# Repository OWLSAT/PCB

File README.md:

# PCB
Place all PCB projects here. Make sure that each PCB project is completely constrained inside of a folder for each!

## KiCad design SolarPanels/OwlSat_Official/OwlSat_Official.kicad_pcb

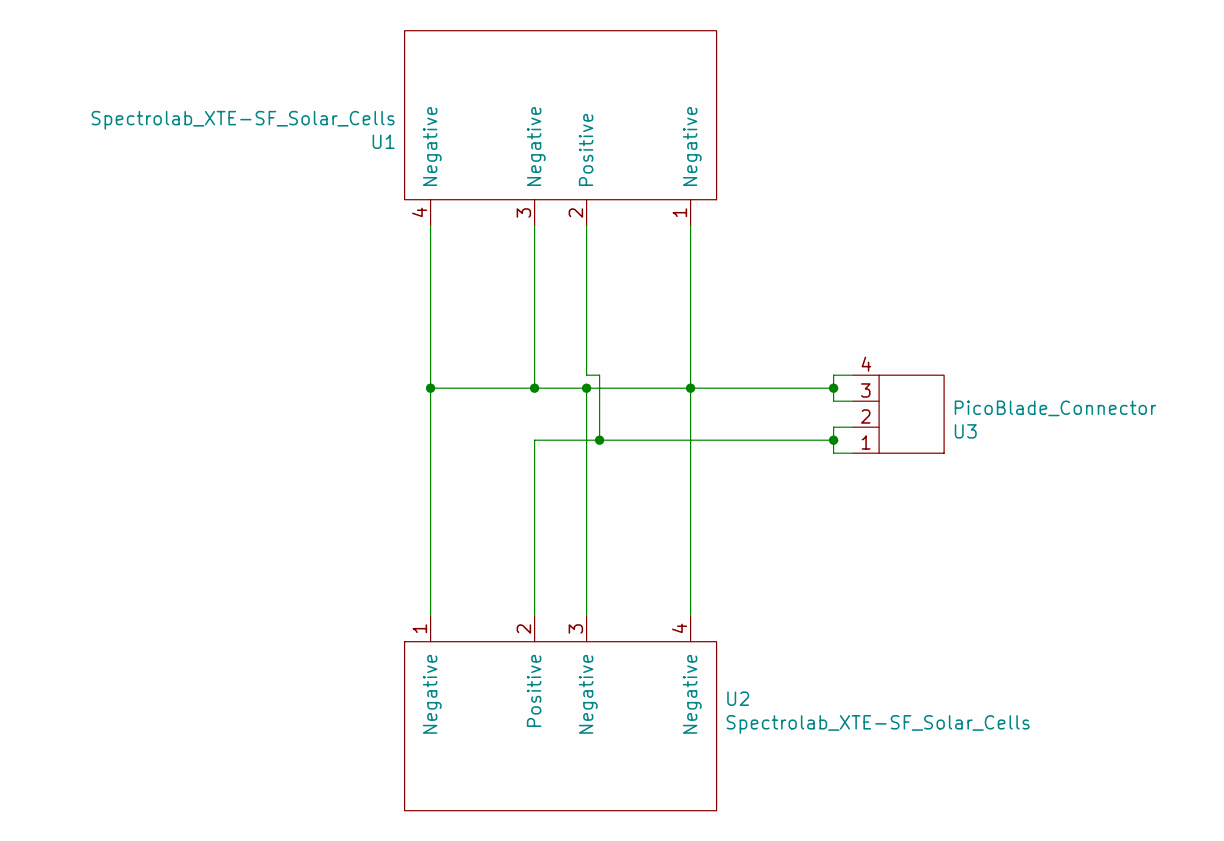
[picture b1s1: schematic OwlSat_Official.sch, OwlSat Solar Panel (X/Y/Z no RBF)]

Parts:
U1, U2: Spectrolab_XTE-SF_Solar_Cells; Spectrolab_XTE-SF_Solar_Cell
U3: PicoBlade_Connector; Molex_PicoBlade_53261-0471_1x04-1MP_P1.25mm_Horizontal

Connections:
unnamed: U1.1 (Negative), U1.3 (Negative), U1.4 (Negative), U2.1 (Negative), U2.3 (Negative), U2.4 (Negative), U3.3, U3.4
unnamed: U1.2 (Positive), U2.2 (Positive), U3.1, U3.2

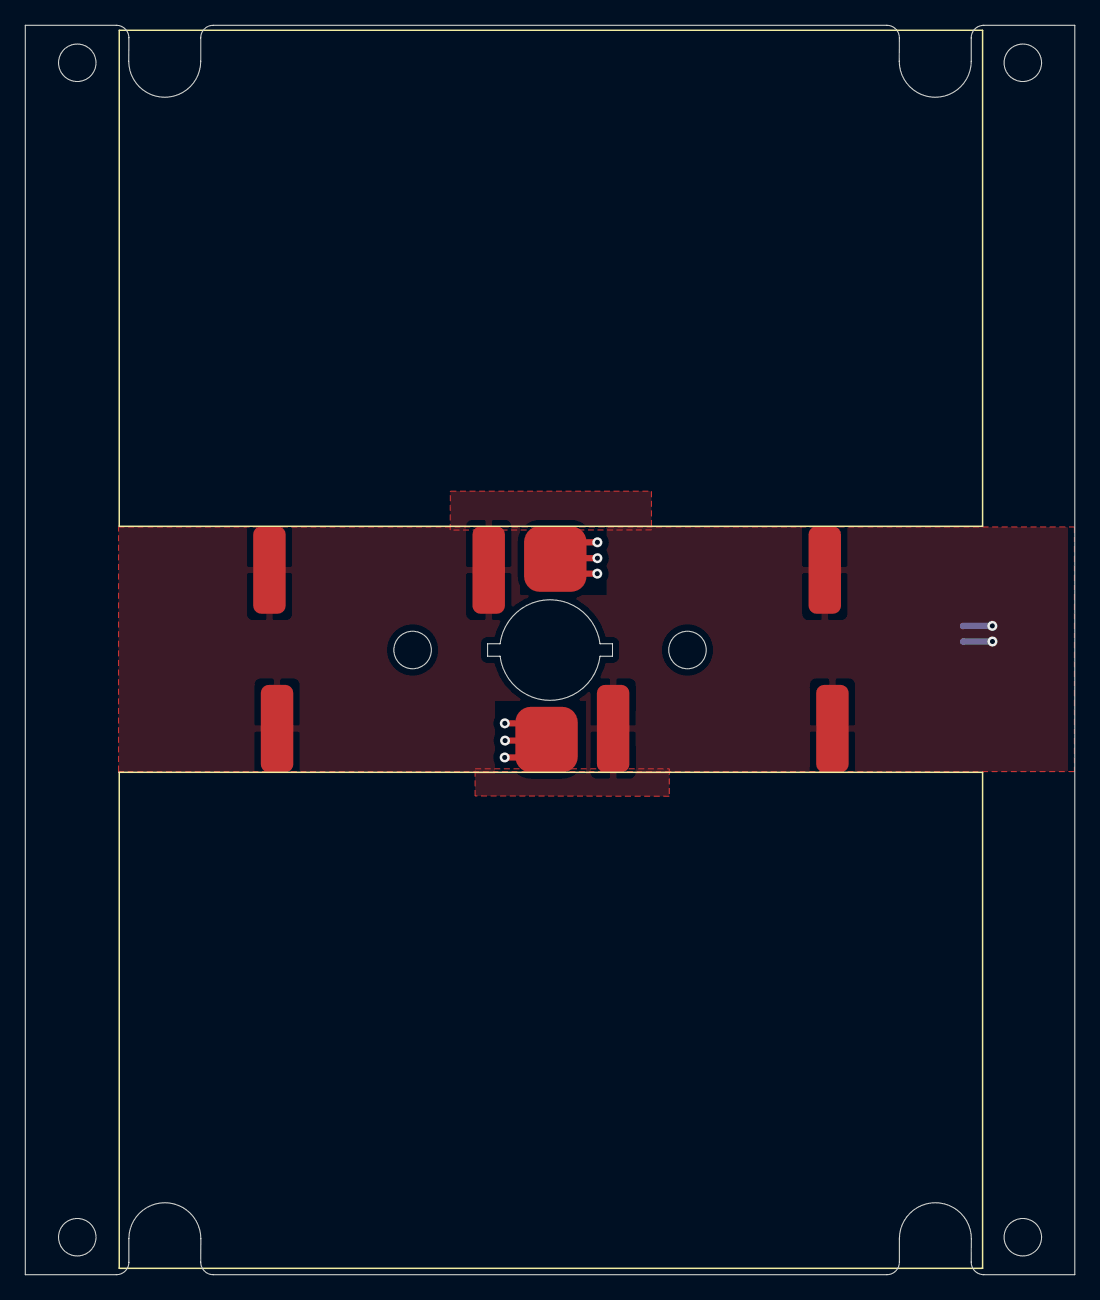
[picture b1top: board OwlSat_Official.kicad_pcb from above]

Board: 2 copper layers, 84.0 x 100.0 mm, 3 parts (1 on the bottom side), 2 nets.

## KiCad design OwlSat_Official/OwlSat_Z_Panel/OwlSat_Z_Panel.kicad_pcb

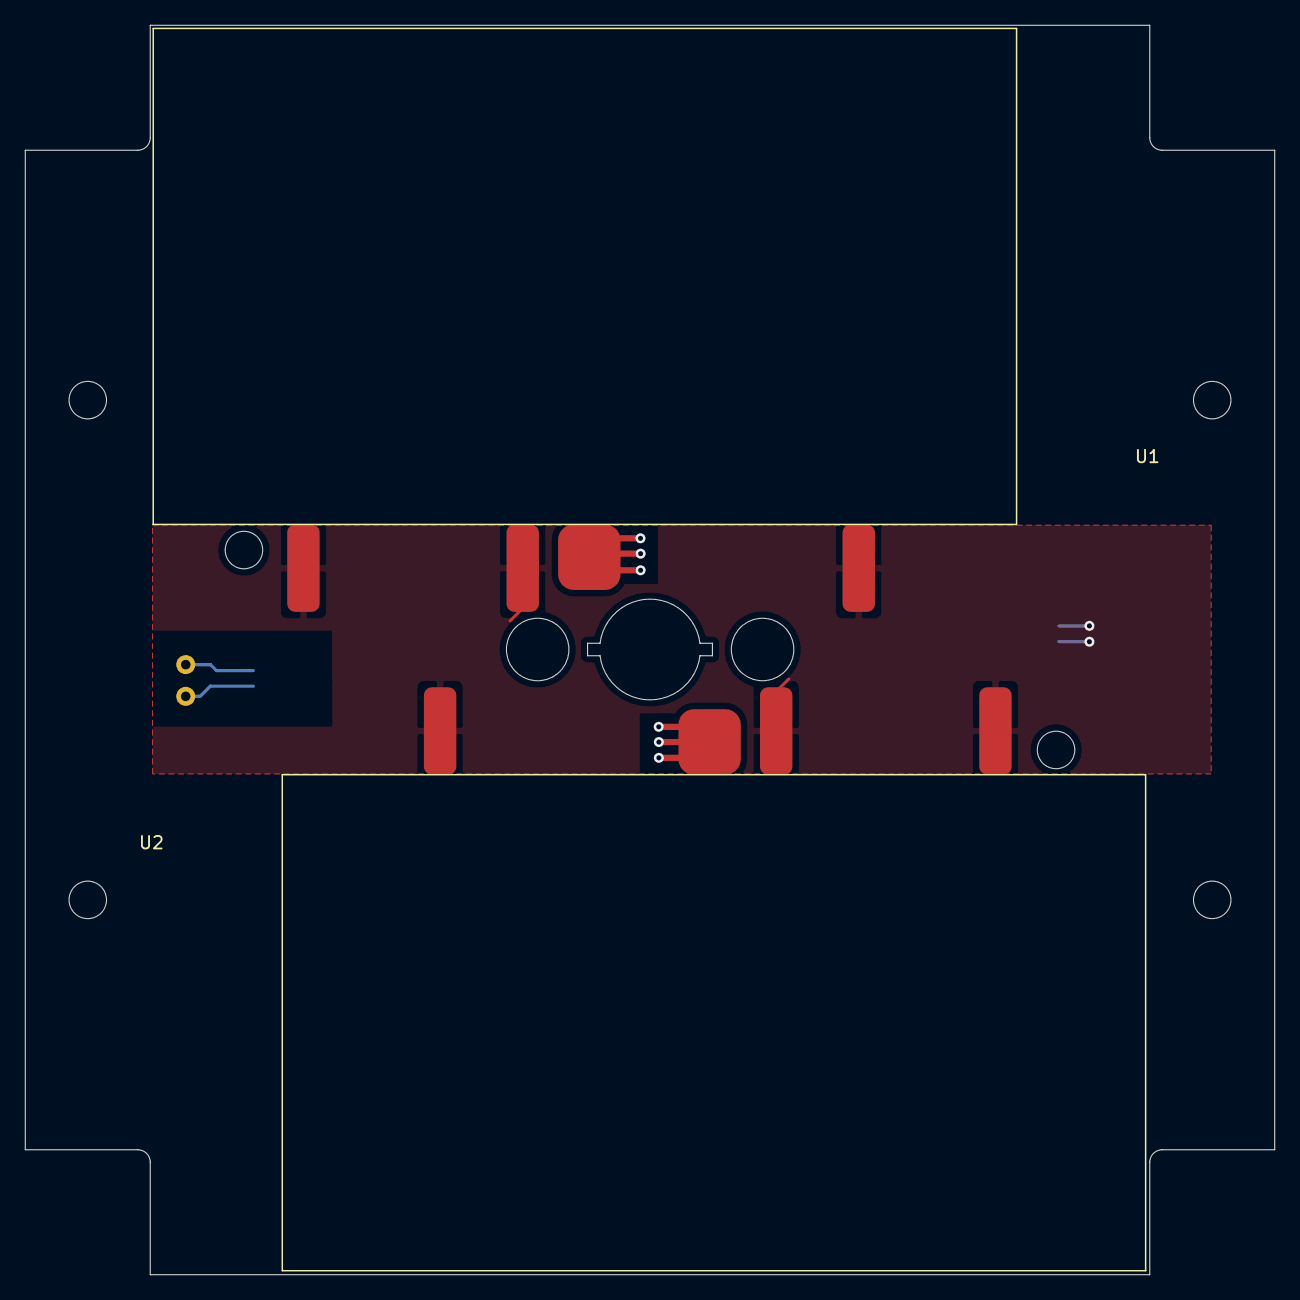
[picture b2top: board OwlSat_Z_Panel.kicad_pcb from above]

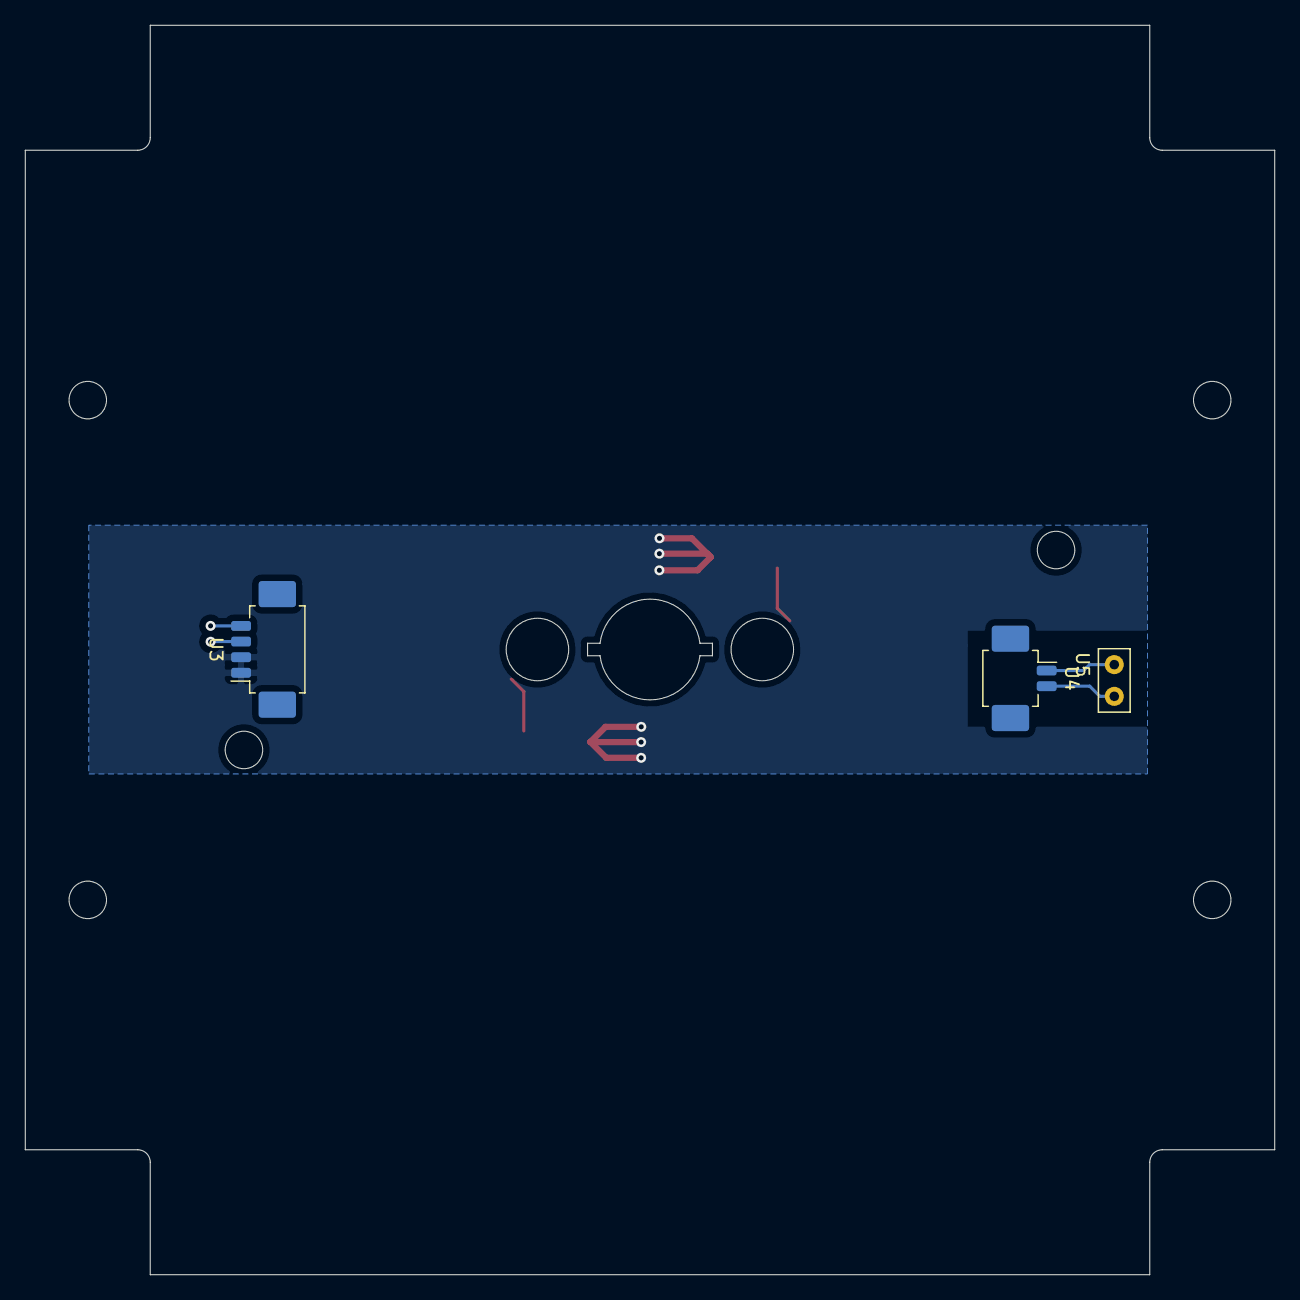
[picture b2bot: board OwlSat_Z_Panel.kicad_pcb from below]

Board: 2 copper layers, 100.0 x 100.0 mm, 5 parts (3 on the bottom side), 4 nets.

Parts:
U1, U2: Spectrolab_XTE-SF_Solar_Cells; Spectrolab_XTE-SF_Solar_Cell
U3: PicoBlade_Connector; Molex_PicoBlade_53261-0471_1x04-1MP_P1.25mm_Horizontal
U4: PicoBlade_2; Molex_PicoBlade_53261-0271_1x02-1MP_P1.25mm_Horizontal
U5: RBF_Pin; RBF

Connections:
unnamed: U1.1, U1.3, U1.4, U2.1, U2.3, U2.4, U3.3, U3.4
unnamed: U1.2, U2.2, U3.1, U3.2
unnamed: U4.1, U5.1
unnamed: U4.2, U5.2

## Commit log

2022-01-30 Added new Antenna Branch. Started Altium Project for Antenna PCB.
2022-01-30 Finished Stackup and impedance profile. Next is to define rules and draw board outline followed by defining footprints and the schematic.
2022-02-03 Finished functional schematic and board outline. Need to add JLPCB design rules and begin routing. Still need mounting holes for elements and chassis.
2022-02-04 Ready to route RF traces
2022-02-09 Routing finished. Last piece before simulation is adding mounting holes.
2022-02-28 Updated .gitignore
2022-02-28 Finished PCB. Fabrication files are next.
2022-02-28 Ready for JLCPCB, but needs to be modified for FR4 and clearance constraints for Sierra Circuits no-touch.
2022-02-28 Ready to fabricate with Sierra Circuits. (baring drill file and ODB++ pass inspection)
2022-02-28 Fixed a clearance issue. Board spec'd at 00 for this configuration.
2022-03-04 Final Solar Panels PCBs. Awaiting confirmation on which board layouts we will need to purchase. This file will be updated accordingly.
2022-03-04 KiCad files for the solar panel PCBs. Access the X/Y panels through the OwlSat_Official.pro (regular pcb has the same name, panels with the USB port has the title USB_actual, and the vent panel is li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
2022-03-05 Modified board to fit no-touch requirements at lowest cost for both Advanced Circuits and Sierra Circuits.
2022-03-11 Sent for fabrication. Pre-fabrication documentation complete.
2022-03-20 After fabrication, found that there were 4 circles added on shifted by 90 degrees of the actual non-plated through holes. The circles are now removed and the fabrication files should be re-generated 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
2022-03-27 Revert "Final Solar Panels PCBs. Awaiting confirmation on which board layouts we will need to purchase. This file will be updated accordingly."
    This reverts commit 9b40886bbc2d796198cd988bcb3e036f41a82efb.
2022-03-27 Revert "KiCad files for the solar panel PCBs. Access the X/Y panels through the OwlSat_Official.pro (regular pcb has the same name, panels with the USB port has the title USB_actual, and the vent pan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
    This reverts commit 130e4a3612c5404f5724af41005bc46dead1946a.
2022-03-27 Fixed the gitignore for the BOM and KiCAD. For some reason my template excluded the BOM and kiCAD netlists.
2022-03-27 Solar Panel PCBs have been designed, purchased, and fabricated.
2022-05-15 Updated documentation to include the testing of the antenna.
2022-05-15 Added notes about L-Matching.
2022-05-28 Revert "Solar Panel PCBs have been designed, purchased, and fabricated."
2022-05-28 Removed Colons from filepaths
2022-05-28 Started work on creating OWLSAT Flight board from PyCubed Mainboard v4.
2022-06-01 Board now has schematic and PCB libraries in Altium and is ready to be edited. The order of the polygon pours was adjusted to ensure the nets are connected just as in the KiCAD project.
2022-06-01 Needed to make another save to all files to confirm the last commit message.
2022-06-08 Removed connectors and sub-circuits marked for removal in the OwlSat flight board floorplan.
2022-06-11 Deleted some more stuff and talked through what to add
2022-06-15 Removed a few more connectors from the schematics, updated the JTAG to be included, and created the header pin component for the stack connection in the schematic and footprint libraries.
2022-06-16 Added schematic symbols for EUV circuits, created circuit on payloads page of mainboard schematic. Will need to update component designators and footprints, as well as connect circuit outputs to corr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
2022-06-17 Corrected footprints and schematic designators of payloads circuit components.
2022-06-19 Added ADCS Magnetorquer Driver Circuit
2022-06-21 Updated with USB mini.
2022-06-23 Fixed duplicate pins and designator issues. Also fixed pad rings around through holes in the stack connector footprint.
2022-06-27 BOM Created
2022-06-28 Added silk screen to stack connector and began cleanup of old PCB traces.
2022-06-28 Cleaned up more old PCB traces.
2022-06-30 Removed more old traces and moved new components out of board area to prepare for layout.
2022-07-01 Fixed a net connection in the Payloads circuits. Began placement of payloads footprints on flightboard. Moved GPS footprints to new location as marked on floorplan.
2022-07-01 Did some minor fixes on rooms and traces on the inner layer.
2022-07-10 Connectors are now correct.
2022-07-10 Removed unused pins from microcontroller. Ready to finish wiring connectors to MCU.
2022-07-11 All wiring is done and confirmed except for EPS_RESET and the connector for the ADCS. Some work needs to be done on the footprint of the JTAG connector to make it match the JTAG programmer cable.
2022-07-15 Added 4-pin Molex connectors to ADCS circuit
2022-07-16 Schematics verified and reviewed. Now under lock control. (Must have 2 people to change schematic unless you are the creator) Ready to route
2022-07-16 Now under lock control after some issues with the JTAG programmer.
2022-07-18 USB routing, JLCPCB 4 layer rules, and stackup finished. Ready to normal routing.
2022-07-18 All violations resolved and ready to route.
2022-07-18 Placed components on board and began routing of easy connections.
2022-07-19 Schematics reviewed with Stone.
2022-07-20 Routed more of the ADCS circuits. Still need to connect to the MCU and complete the connections to the external ports.
2022-07-21 Completed more routing to the MCU. Began routing ground pins.
2022-07-25 Stackable connector in position.
2022-07-31 Did some routing. Slowly working torward completion.
2022-07-31 Added actual footprint or board connector (accidentally did a socket instead of a header). Much routing done.
2022-08-01 Replaced connectors with vertical connectors. No longer doing stackable either.
2022-08-04 Routed ADCS Circuit and Burn Wires.
2022-08-06 Routing finished, but need to swap power plane from top to bottom to reduce EMI because of the magnetorquer above the board.
2022-08-06 Finished Routing. Now need to add USB regulator IC to power board for programming.
2022-08-24 Project ready to hand off to underclassmen since I have a chip tapeout. All that is needed is chip potentiometers on the EUV circuit to allow for gain and bias tuning.
2022-08-24 Now ready to hand off to undergrads to finish up.
2022-08-29 Added digital potentiometers to the EUV amplifiers for gain and bias voltage control
2022-08-31 Getting weird pin errors - cannot route
2022-08-31 New push with error
2022-08-31 Error with potentiometer footprint fixed.
2022-09-01 Routed digital potentiometer parts
2022-09-06 Minor corrections and cleanup
2022-09-07 Finished clearing DRC errors
2022-09-07 Last BOM corrections and fixed trace width on burn wire circuit
2022-09-24 Post-Fabrication: Fixed some MPN issues and removed all Altium Content Valut parts that should have never been used! Will most likely edit the silkscreen for future prints, so that it is professional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
2022-10-04 Chanded MCU to 64-VQFN instead of 64-TQFP (the PyBadge scavenged MCU have no leads as found by Nick)
2022-11-18 Fixed Silkscreen. Needs to have amplifier replaced to satisfy science team requirements. An IC amplifier will be required.
2022-11-18 Added Allen's Notes to the project.
2023-04-09 Schematic: Implemented new transconductance amplifier circuit array
2023-04-10 Completed layout and exported GRB files
